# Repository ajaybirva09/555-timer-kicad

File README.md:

# 555 Timer Audio Tone Generator

## 📌 Overview
This project is an audio tone generator circuit designed using KiCad 9.0.
It uses the LM555 timer IC in astable mode to produce a continuous tone
which is output through a speaker.

## 🔧 Functionality
- Generates an audible square wave using a 555 timer
- Speaker output through coupling capacitor
- Frequency determined by R1, R2, C1 network

## 🧩 Components
| Component | Value |
|-----------|--------|
| LM555 Timer | 1 |
| Resistor R1 | 4.7kΩ |
| Resistor R2 | 100kΩ |
| Capacitor C1 | 0.1µF |
| Capacitor C2 | 10µF |
| Speaker | 8Ω |

## 🛠 Designed With
- KiCad 9.0

## 🖼 Project Images

### 🔹 Schematic

### 🔹 PCB Layout

### 🔹 PCB 3D View

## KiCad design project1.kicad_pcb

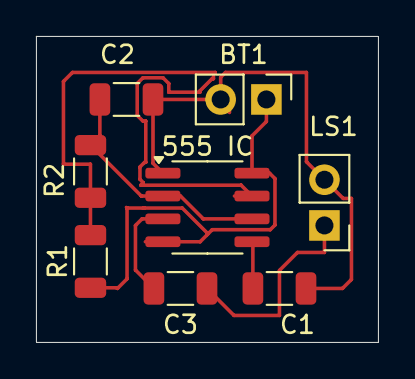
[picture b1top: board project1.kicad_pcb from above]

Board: 2 copper layers, 19.0 x 17.0 mm, 8 parts (0 on the bottom side), 7 nets.

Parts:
555 IC: LM555xM; SOIC-8_3.9x4.9mm_P1.27mm
BT1: PinHeader_1x02_P2.54mm_Vertical
C1: 0.1uf; C_1206_3216Metric
C2: 0.1u; C_1206_3216Metric
C3: 10uf; C_1206_3216Metric
LS1: Speaker; PinHeader_1x02_P2.54mm_Vertical
R1: 4.7k; R_1206_3216Metric
R2: 100k; R_1206_3216Metric

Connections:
GND: 555 IC.1 (GND), BT1.2 (-), C1.2, C2.2, LS1.2
unnamed: C3.2, LS1.1
unnamed: 555 IC.5 (CV), C1.1
unnamed: 555 IC.7 (DIS), R1.2, R2.1
unnamed: 555 IC.3 (Q), C3.1
trig: 555 IC.2 (TR), 555 IC.6 (THR), C2.1, R2.2
vcc: 555 IC.4 (R), 555 IC.8 (VCC), BT1.1 (+), R1.1

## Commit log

2026-01-01 Add files via upload
    Added schematic, PCB layout and 3D view images
